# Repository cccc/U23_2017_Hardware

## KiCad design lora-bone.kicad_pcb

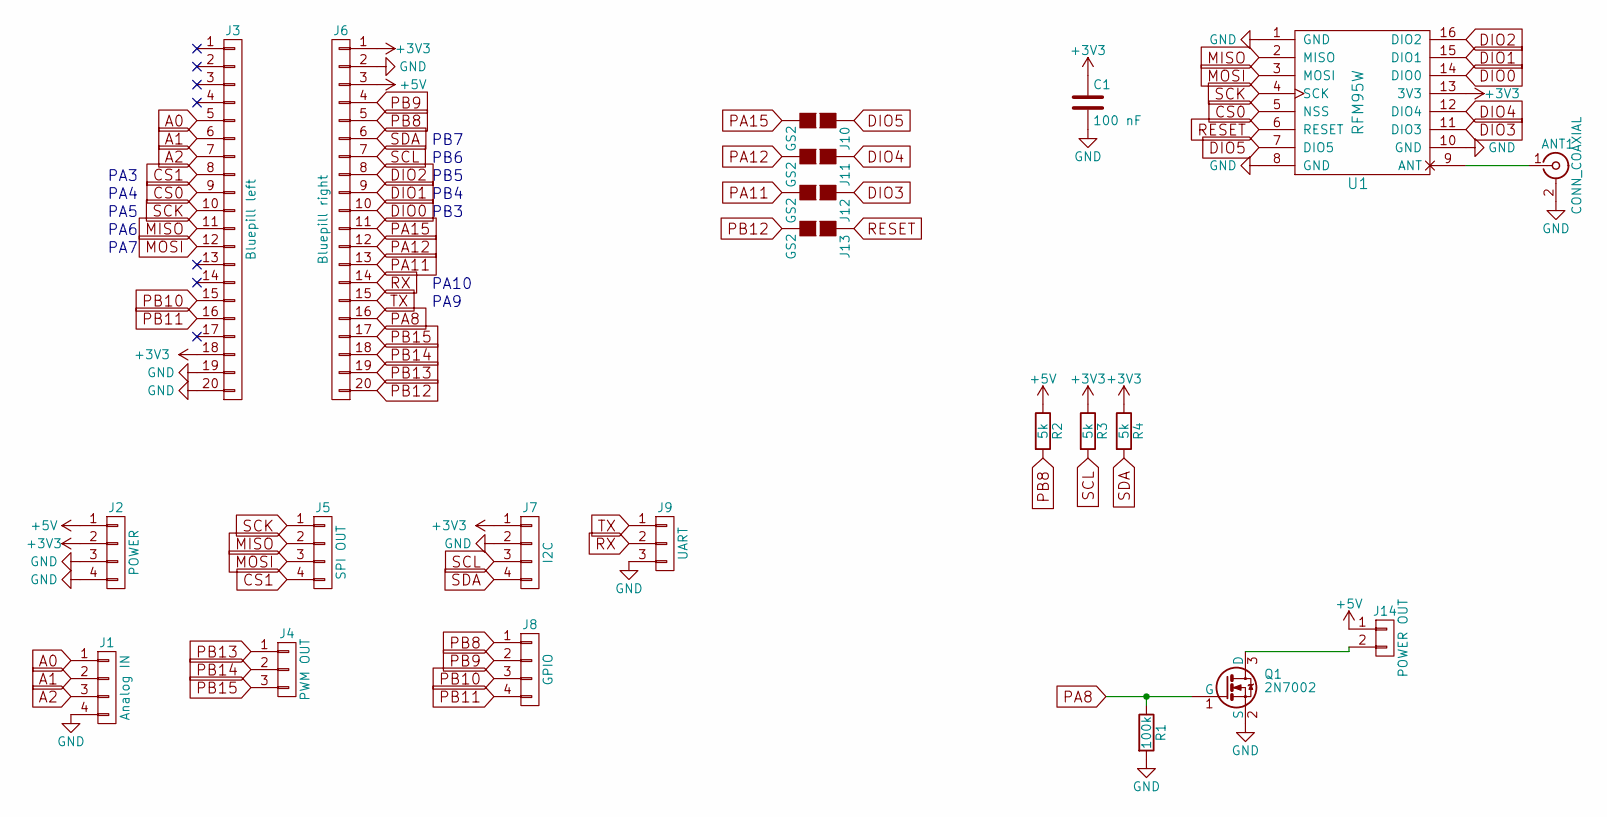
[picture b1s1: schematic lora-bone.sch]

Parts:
ANT1: CONN_COAXIAL; SMA_THT_Jack_Straight
C1: 100 nF; C_0805_HandSoldering
J1: Analog IN; Pin_Header_Straight_1x04_Pitch2.54mm
J2: POWER; Pin_Header_Straight_1x04_Pitch2.54mm
J3: Bluepill left; Pin_Header_Straight_1x20_Pitch2.54mm
J4: PWM OUT; Pin_Header_Straight_1x03_Pitch2.54mm
J5: SPI OUT; Pin_Header_Straight_1x04_Pitch2.54mm
J6: Bluepill right; Pin_Header_Straight_1x20_Pitch2.54mm
J7: I2C; Pin_Header_Straight_1x04_Pitch2.54mm
J8: GPIO; Pin_Header_Straight_1x04_Pitch2.54mm
J9: UART; Pin_Header_Straight_1x03_Pitch2.54mm
J10, J11, J12, J13: GS2
J14: POWER OUT; Pin_Header_Straight_1x02_Pitch2.54mm
Q1: 2N7002; SOT-23_Handsoldering
R1: 100k; R_0805_HandSoldering
R2, R3, R4: 5k; R_0805_HandSoldering
U1: RFM95W; RFM95W_SMD

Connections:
+3V3: C1.1, J2.2, J3.18, J6.1, J7.1, R3.1, R4.1, U1.13 (3V3)
+5V: J2.1, J6.3, J14.1, R2.1
A0: J1.1, J3.5
A1: J1.2, J3.6
A2: J1.3, J3.7
CS0: J3.9, U1.5 (NSS)
CS1: J3.8, J5.4
DIO0: J6.10, U1.14 (DIO0)
DIO1: J6.9, U1.15 (DIO1)
DIO2: J6.8, U1.16 (DIO2)
DIO3: J12.1 (G1), U1.11 (DIO3)
DIO4: J11.1 (G1), U1.12 (DIO4)
DIO5: J10.1 (G1), U1.7 (DIO5)
GND: ANT1.2 (Ext), C1.2, J1.4, J2.3, J2.4, J3.19, J3.20, J6.2, J7.2, J9.3, Q1.2 (S), R1.2, U1.1 (GND), U1.8 (GND), U1.10 (GND)
MISO: J3.11, J5.2, U1.2 (MISO)
MOSI: J3.12, J5.3, U1.3 (MOSI)
unnamed: ANT1.1 (In), U1.9 (ANT)
unnamed: J14.2, Q1.3 (D)
PA8: J6.16, Q1.1 (G), R1.1
PA11: J6.13, J12.2 (G2)
PA12: J6.12, J11.2 (G2)
PA15: J6.11, J10.2 (G2)
PB8: J6.5, J8.1, R2.2
PB9: J6.4, J8.2
PB10: J3.15, J8.3
PB11: J3.16, J8.4
PB12: J6.20, J13.2 (G2)
PB13: J4.1, J6.19
PB14: J4.2, J6.18
PB15: J4.3, J6.17
RESET: J13.1 (G1), U1.6 (RESET)
RX: J6.14, J9.2
SCK: J3.10, J5.1, U1.4 (SCK)
SCL: J6.7, J7.3, R3.2
SDA: J6.6, J7.4, R4.2
TX: J6.15, J9.1

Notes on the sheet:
PA7
PA6
PA5
PA4
PA3
PB7
PB6
PB5
PB3
PB4
PA10
PA9

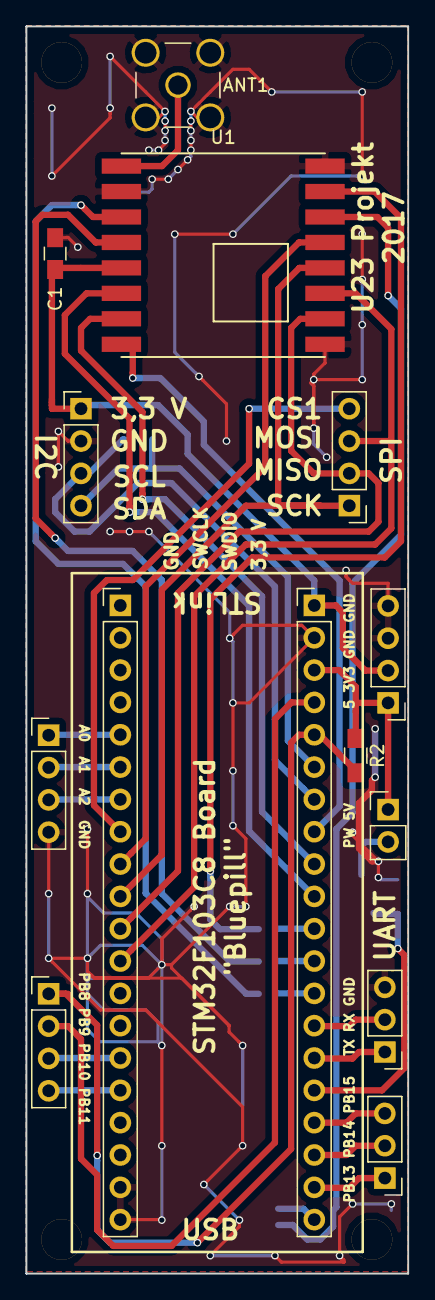
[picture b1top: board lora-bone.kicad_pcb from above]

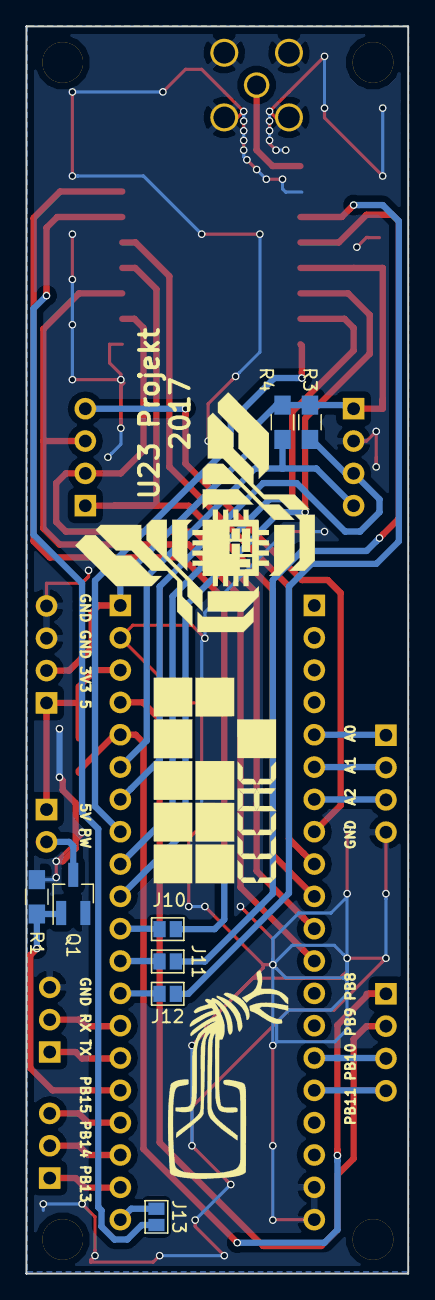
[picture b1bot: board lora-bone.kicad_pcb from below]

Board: 2 copper layers, 30.0 x 98.0 mm, 22 parts (8 on the bottom side), 36 nets.

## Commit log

2017-09-03 Initial Commit
    Did already most of PCB Design. Some Labels are missing. Maybe an "Power GPIO" will be added by Ike
2017-09-04 More Labeles for Breakout Header
2017-09-04 A few little corrections
2017-09-04 Nicer Ground Planes, nicer Via placements, hopefully better Ground Distribution :>
2017-09-04 More Logos.
    There can never be enough logos. It is not possible to reduce the count of Logos
2017-09-04 A few changes and corrections
2017-09-04 Add power GPIO hint
2017-09-04 Power GPIO routet. Added Pull UP Resistor for PB8
2017-09-04 Added Pull Ups for I2C.
2017-09-05 moved CCCAC Logo a bit, deactivated one reference
2017-09-24 Make the Board 2 mm shorter
2017-09-24 Created panelized Gerber Files for dirtypcbs
2017-09-24 Added the final gerber files and Schematic as PDF
2017-10-16 Made RFM95W Footprint slighty better for components diagramm
2017-10-16 Exported components diagramm as svg
2017-10-16 Made Components diagramm with BOM as tex document
2017-10-16 Moved schematics pdf to doku/
2017-10-16 Added LICENSE.TXT
2017-10-16 Make rfm95w footprint even better
